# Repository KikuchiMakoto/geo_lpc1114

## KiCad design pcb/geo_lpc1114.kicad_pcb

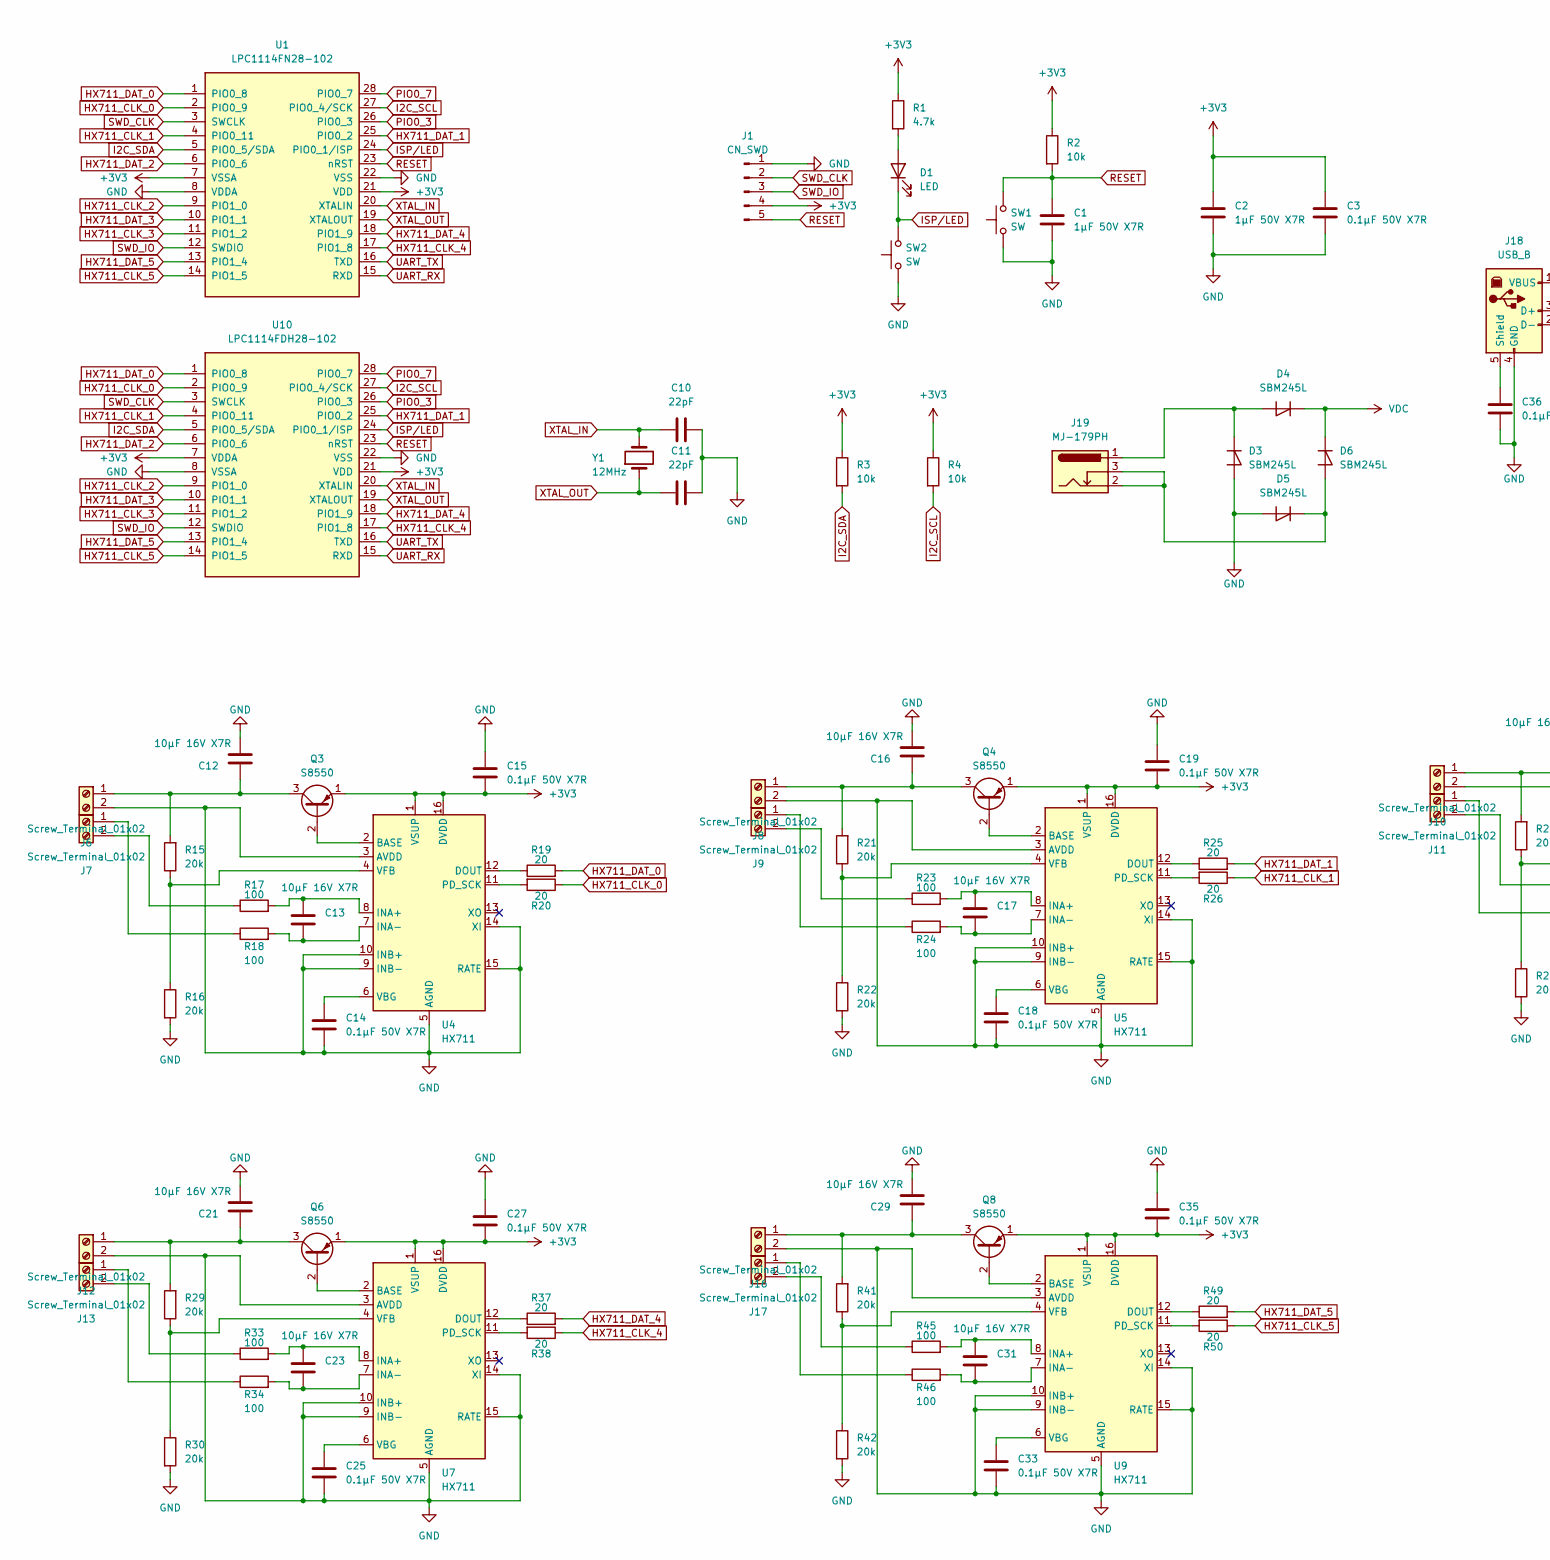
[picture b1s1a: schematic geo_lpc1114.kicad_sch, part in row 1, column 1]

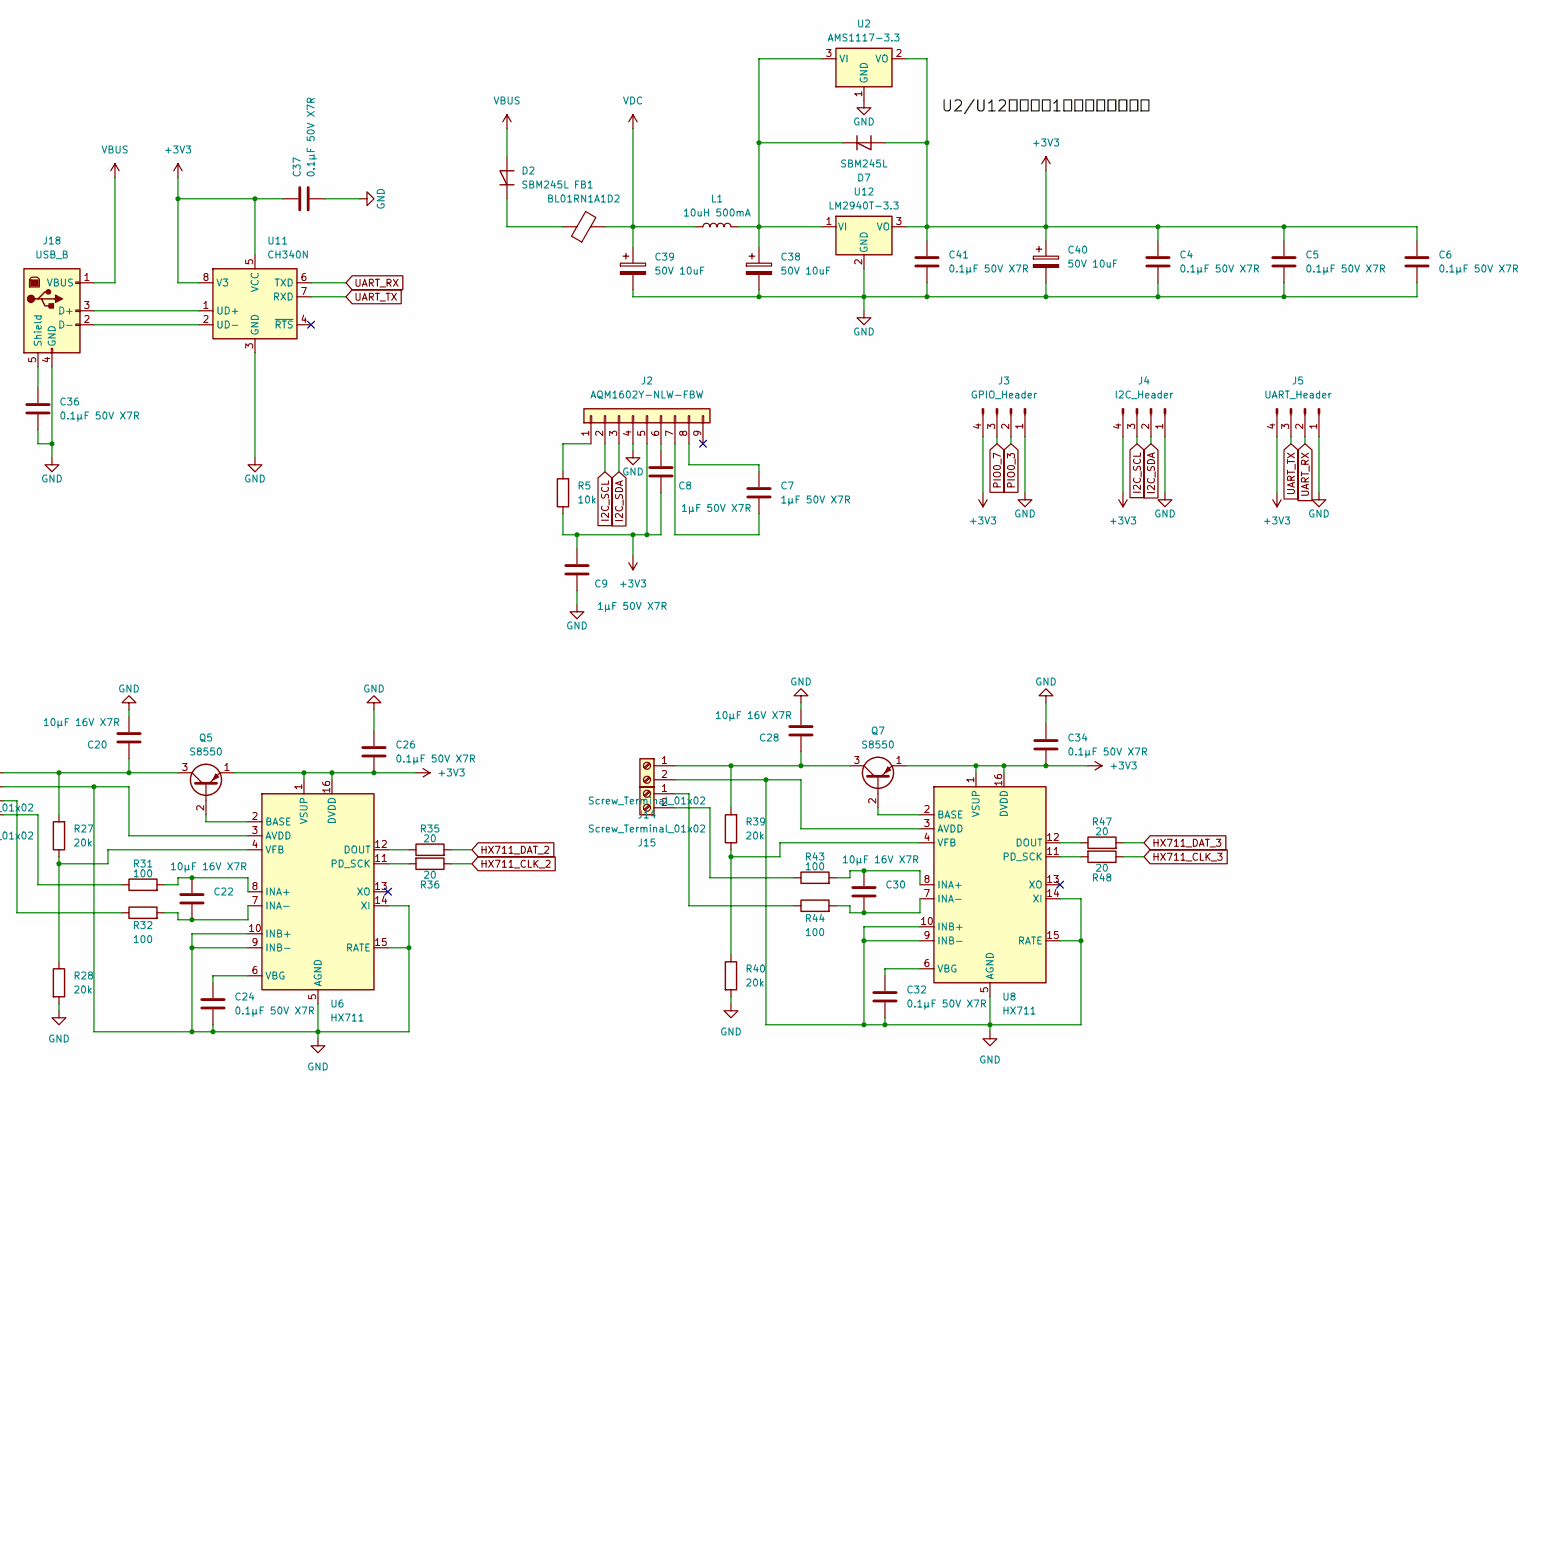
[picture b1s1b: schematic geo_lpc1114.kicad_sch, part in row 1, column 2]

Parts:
C1, C2: 1μF 50V X7R; C_Disc_D5.1mm_W3.2mm_P5.00mm
C3, C4, C5, C6, C14, C15, C18, C19, C24, C25, C26, C27, C32, C33, C34, C35, C36, C37, C41: 0.1μF 50V X7R; C_Disc_D3.8mm_W2.6mm_P2.50mm
C7, C8, C9: 1μF 50V X7R; C_Disc_D4.3mm_W1.9mm_P5.00mm
C10, C11: 22pF; C_Disc_D4.3mm_W1.9mm_P5.00mm
C12, C13, C16, C17, C20, C21, C22, C23, C28, C29, C30, C31: 10μF 16V X7R; C_Disc_D5.1mm_W3.2mm_P5.00mm
C38, C39, C40: 50V 10uF; CP_Radial_D5.0mm_P2.00mm
D1: LED; LED_D3.0mm
D2, D3, D4, D5, D6, D7: SBM245L; D_DO-41_SOD81_P7.62mm_Horizontal
FB1: BL01RN1A1D2; L_Axial_L5.0mm_D3.6mm_P10.00mm_Horizontal_Murata_BL01RN1A2A2
J1: CN_SWD; PinHeader_1x05_P2.54mm_Vertical
J2: AQM1602Y-NLW-FBW; PinHeader_1x09_P2.54mm_Vertical
J3: GPIO_Header; PinHeader_1x04_P2.54mm_Vertical
J4: I2C_Header; PinHeader_1x04_P2.54mm_Vertical
J5: UART_Header; PinHeader_1x04_P2.54mm_Vertical
J6, J7, J8, J9, J10, J11, J12, J13, J14, J15, J16, J17: Screw_Terminal_01x02; TerminalBlock_Xinya_XY308-2.54-2P_1x02_P2.54mm_Horizontal
J18: USB_B; USB_B_OST_USB-B1HSxx_Horizontal
J19: MJ-179PH; BarrelJack_Horizontal
L1: 10uH 500mA; L_Axial_L5.0mm_D3.6mm_P10.00mm_Horizontal_Murata_BL01RN1A2A2
Q3, Q4, Q5, Q6, Q7, Q8: S8550; TO-92_HandSolder
R1: 4.7k; R_Axial_DIN0204_L3.6mm_D1.6mm_P7.62mm_Horizontal
R2, R3, R4, R5: 10k; R_Axial_DIN0204_L3.6mm_D1.6mm_P7.62mm_Horizontal
R15, R16, R21, R22, R27, R28, R29, R30, R39, R40, R41, R42: 20k; R_Axial_DIN0204_L3.6mm_D1.6mm_P7.62mm_Horizontal
R17, R18, R23, R24, R31, R32, R33, R34, R43, R44, R45, R46: 100; R_Axial_DIN0204_L3.6mm_D1.6mm_P7.62mm_Horizontal
R19, R20, R25, R26, R35, R36, R37, R38, R47, R48, R49, R50: 20; R_Axial_DIN0204_L3.6mm_D1.6mm_P7.62mm_Horizontal
SW1, SW2: SW; SW_TH_Tactile_Omron_B3F-100x
U1: LPC1114FN28-102; DIP-28_W15.24mm_LongPads
U2: AMS1117-3.3; SOT-223-3_TabPin2
U4, U5, U6, U7, U8, U9: HX711; SOIC-16_3.9x9.9mm_P1.27mm
U10: LPC1114FDH28-102; TSSOP-28_4.4x9.7mm_P0.65mm
U11: CH340N; JEITA_SOIC-8_3.9x4.9mm_P1.27mm
U12: LM2940T-3.3; TO-220-3_Horizontal_TabDown
Y1: 12MHz; Crystal_HC49-U_Vertical

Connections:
+3V3: C2.1, C3.1, C4.1, C5.1, C6.1, C8.2, C9.1, C15.2, C19.2, C26.2, C27.2, C34.2, C35.2, C37.1, C40.1, C41.1, D7.2 (A), J1.4, J2.5, J3.4, J4.4, J5.4, Q3.1 (E), Q4.1 (E), Q5.1 (E), Q6.1 (E), Q7.1 (E), Q8.1 (E), R1.1, R2.1, R3.1, R4.1, R5.1, U1.7 (VSSA), U1.21 (VDD), U2.2 (VO), U4.1 (VSUP), U4.16 (DVDD), U5.1 (VSUP), U5.16 (DVDD), U6.1 (VSUP), U6.16 (DVDD), U7.1 (VSUP), U7.16 (DVDD), U8.1 (VSUP), U8.16 (DVDD), U9.1 (VSUP), U9.16 (DVDD), U10.7 (VDDA), U10.21 (VDD), U11.5 (VCC), U11.8 (V3), U12.3 (VO)
GND: C1.2, C2.2, C3.2, C4.2, C5.2, C6.2, C9.2, C10.2, C11.2, C12.2, C14.2, C15.1, C16.2, C18.2, C19.1, C20.2, C21.2, C24.2, C25.2, C26.1, C27.1, C28.2, C29.2, C32.2, C33.2, C34.1, C35.1, C36.2, C37.2, C38.2, C39.2, C40.2, C41.2, D3.2 (A), D5.2 (A), J1.1, J2.4, J3.1, J4.1, J5.1, J6.2, J8.2, J10.2, J12.2, J14.2, J16.2, J18.4 (GND), R16.2, R22.2, R28.2, R30.2, R40.2, R42.2, SW1.1, SW2.1, U1.8 (VDDA), U1.22 (VSS), U2.1 (GND), U4.3 (AVDD), U4.5 (AGND), U4.9 (INB-), U4.10 (INB+), U4.14 (XI), U4.15 (RATE), U5.3 (AVDD), U5.5 (AGND), U5.9 (INB-), U5.10 (INB+), U5.14 (XI), U5.15 (RATE), U6.3 (AVDD), U6.5 (AGND), U6.9 (INB-), U6.10 (INB+), U6.14 (XI), U6.15 (RATE), U7.3 (AVDD), U7.5 (AGND), U7.9 (INB-), U7.10 (INB+), U7.14 (XI), U7.15 (RATE), U8.3 (AVDD), U8.5 (AGND), U8.9 (INB-), U8.10 (INB+), U8.14 (XI), U8.15 (RATE), U9.3 (AVDD), U9.5 (AGND), U9.9 (INB-), U9.10 (INB+), U9.14 (XI), U9.15 (RATE), U10.8 (VSSA), U10.22 (VSS), U11.3 (GND), U12.2 (GND)
HX711_CLK_0: R20.1, U1.2 (PIO0_9), U10.2 (PIO0_9)
HX711_CLK_1: R26.1, U1.4 (PIO0_11), U10.4 (PIO0_11)
HX711_CLK_2: R36.1, U1.9 (PIO1_0), U10.9 (PIO1_0)
HX711_CLK_3: R48.1, U1.11 (PIO1_2), U10.11 (PIO1_2)
HX711_CLK_4: R38.1, U1.17 (PIO1_8), U10.17 (PIO1_8)
HX711_CLK_5: R50.1, U1.14 (PIO1_5), U10.14 (PIO1_5)
HX711_DAT_0: R19.2, U1.1 (PIO0_8), U10.1 (PIO0_8)
HX711_DAT_1: R25.2, U1.25 (PIO0_2), U10.25 (PIO0_2)
HX711_DAT_2: R35.2, U1.6 (PIO0_6), U10.6 (PIO0_6)
HX711_DAT_3: R47.2, U1.10 (PIO1_1), U10.10 (PIO1_1)
HX711_DAT_4: R37.2, U1.18 (PIO1_9), U10.18 (PIO1_9)
HX711_DAT_5: R49.2, U1.13 (PIO1_4), U10.13 (PIO1_4)
I2C_SCL: J2.2, J4.3, R4.2, U1.27 (PIO0_4/SCK), U10.27 (PIO0_4/SCK)
I2C_SDA: J2.3, J4.2, R3.2, U1.5 (PIO0_5/SDA), U10.5 (PIO0_5/SDA)
ISP/LED: D1.1 (K), SW2.2, U1.24 (PIO0_1/ISP), U10.24 (PIO0_1/ISP)
unnamed: D1.2 (A), R1.2
unnamed: D2.1 (K), FB1.1
unnamed: D3.1 (K), D4.2 (A), J19.1
unnamed: D5.1 (K), D6.2 (A), J19.2, J19.3
unnamed: C38.1, D7.1 (K), L1.2, U2.3 (VI), U12.1 (VI)
unnamed: J2.1, R5.2
unnamed: C8.1, J2.6
unnamed: C7.2, J2.7
unnamed: C7.1, J2.8
unnamed: C12.1, J6.1, Q3.3 (C), R15.2
unnamed: J7.1, R18.1
unnamed: J7.2, R17.1
unnamed: C16.1, J8.1, Q4.3 (C), R21.2
unnamed: J9.1, R24.1
unnamed: J9.2, R23.1
unnamed: C20.1, J10.1, Q5.3 (C), R27.2
unnamed: J11.1, R32.1
unnamed: J11.2, R31.1
unnamed: C21.1, J12.1, Q6.3 (C), R29.2
unnamed: J13.1, R34.1
unnamed: J13.2, R33.1
unnamed: C28.1, J14.1, Q7.3 (C), R39.2
unnamed: J15.1, R44.1
unnamed: J15.2, R43.1
unnamed: C29.1, J16.1, Q8.3 (C), R41.2
unnamed: J17.1, R46.1
unnamed: J17.2, R45.1
unnamed: J18.3 (D+), U11.1 (UD+)
unnamed: J18.2 (D-), U11.2 (UD-)
unnamed: C36.1, J18.5 (Shield)
unnamed: Q3.2 (B), U4.2 (BASE)
unnamed: Q4.2 (B), U5.2 (BASE)
unnamed: Q5.2 (B), U6.2 (BASE)
unnamed: Q6.2 (B), U7.2 (BASE)
unnamed: Q7.2 (B), U8.2 (BASE)
unnamed: Q8.2 (B), U9.2 (BASE)
unnamed: R19.1, U4.12 (DOUT)
unnamed: C13.1, R17.2, U4.8 (INA+)
unnamed: C13.2, R18.2, U4.7 (INA-)
unnamed: R20.2, U4.11 (PD_SCK)
unnamed: C14.1, U4.6 (VBG)
unnamed: R15.1, R16.1, U4.4 (VFB)
unnamed: R25.1, U5.12 (DOUT)
unnamed: C17.1, R23.2, U5.8 (INA+)
unnamed: C17.2, R24.2, U5.7 (INA-)
unnamed: R26.2, U5.11 (PD_SCK)
unnamed: C18.1, U5.6 (VBG)
unnamed: R21.1, R22.1, U5.4 (VFB)
unnamed: R35.1, U6.12 (DOUT)
unnamed: C22.1, R31.2, U6.8 (INA+)
unnamed: C22.2, R32.2, U6.7 (INA-)
unnamed: R36.2, U6.11 (PD_SCK)
unnamed: C24.1, U6.6 (VBG)
unnamed: R27.1, R28.1, U6.4 (VFB)
unnamed: R37.1, U7.12 (DOUT)
unnamed: C23.1, R33.2, U7.8 (INA+)
unnamed: C23.2, R34.2, U7.7 (INA-)
unnamed: R38.2, U7.11 (PD_SCK)
unnamed: C25.1, U7.6 (VBG)
unnamed: R29.1, R30.1, U7.4 (VFB)
unnamed: R47.1, U8.12 (DOUT)
unnamed: C30.1, R43.2, U8.8 (INA+)
unnamed: C30.2, R44.2, U8.7 (INA-)
unnamed: R48.2, U8.11 (PD_SCK)
unnamed: C32.1, U8.6 (VBG)
unnamed: R39.1, R40.1, U8.4 (VFB)
unnamed: R49.1, U9.12 (DOUT)
unnamed: C31.1, R45.2, U9.8 (INA+)
unnamed: C31.2, R46.2, U9.7 (INA-)
unnamed: R50.2, U9.11 (PD_SCK)
unnamed: C33.1, U9.6 (VBG)
unnamed: R41.1, R42.1, U9.4 (VFB)
PIO0_3: J3.2, U1.26 (PIO0_3), U10.26 (PIO0_3)
PIO0_7: J3.3, U1.28 (PIO0_7), U10.28 (PIO0_7)
RESET: C1.1, J1.5, R2.2, SW1.2, U1.23 (nRST), U10.23 (nRST)
SWD_CLK: J1.2, U1.3 (SWCLK), U10.3 (SWCLK)
SWD_IO: J1.3, U1.12 (SWDIO), U10.12 (SWDIO)
UART_RX: J5.2, U1.15 (RXD), U10.15 (RXD), U11.6 (TXD)
UART_TX: J5.3, U1.16 (TXD), U10.16 (TXD), U11.7 (RXD)
VBUS: D2.2 (A), J18.1 (VBUS)
VDC: C39.1, D4.1 (K), D6.1 (K), FB1.2, L1.1
XTAL_IN: C10.1, U1.20 (XTALIN), U10.20 (XTALIN), Y1.2
XTAL_OUT: C11.1, U1.19 (XTALOUT), U10.19 (XTALOUT), Y1.1

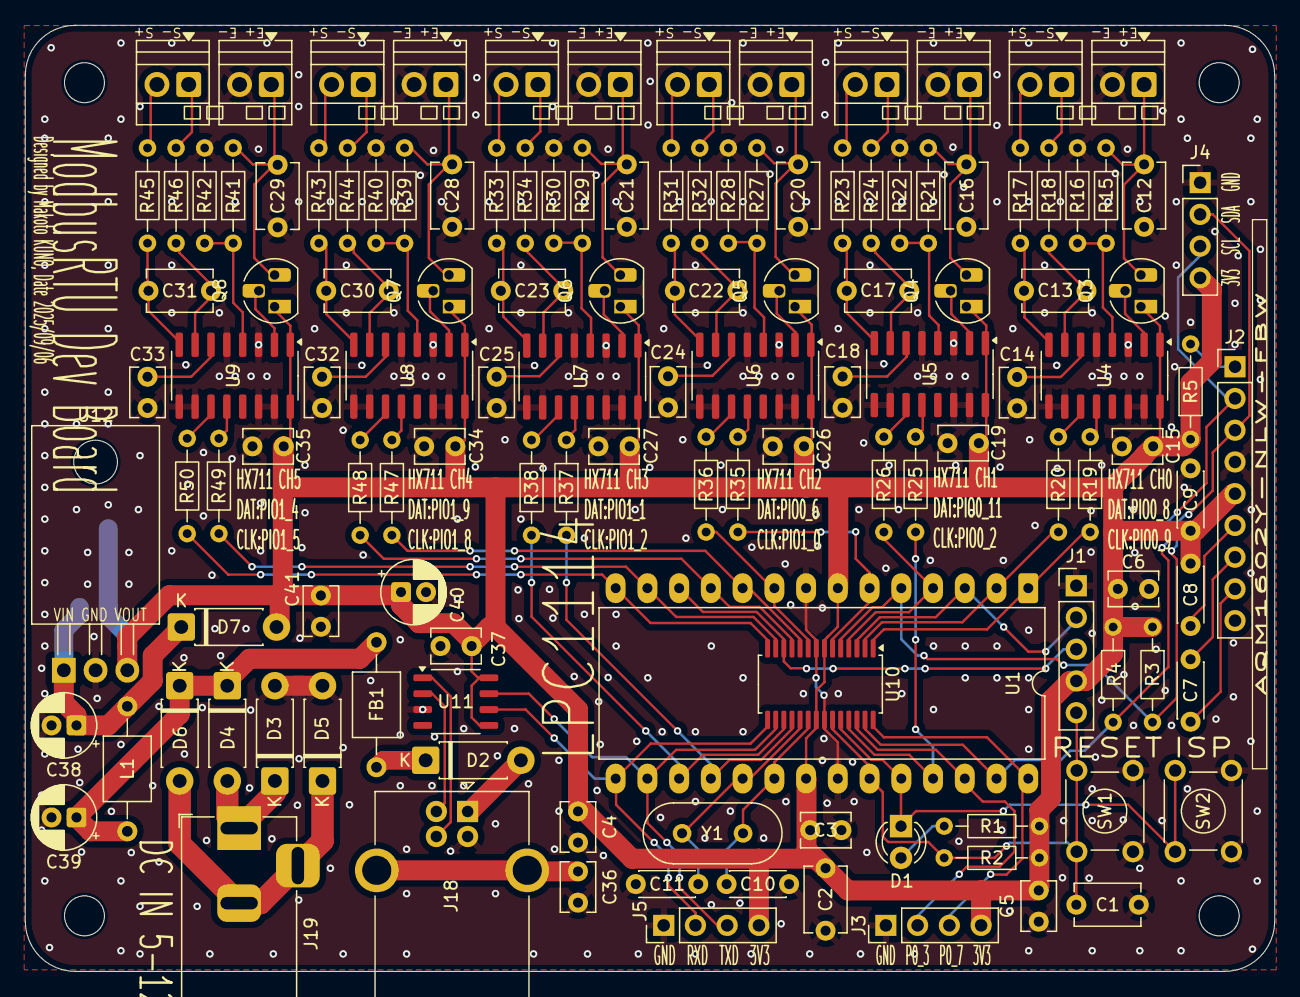
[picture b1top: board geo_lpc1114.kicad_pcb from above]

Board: 2 copper layers, 100.0 x 75.7 mm, 131 parts (1 on the bottom side), 100 nets.

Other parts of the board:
M3: MountingHole_3.2mm_M3

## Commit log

2025-09-05 8ch but forgot OpenDrain I2C Pin...
2025-09-10 fubriaction version 2024/09 1st week
2025-09-15 move dir & Fix VDDA/VSSA pin mapping
2025-09-15 LPCXpresso 版のメモリ消費メモを追加
2025-09-15 ビルド通ったけど動作しない版、ボードの正常確認は終了している
2025-09-15 AMS1117の裏面サブ実装、基盤の角丸め、ほか微修正
